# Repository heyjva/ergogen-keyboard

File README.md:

# ergogen-keyboard

Ergogen keyboard project, migrated to **KiCad 8** with a local preview/edit app.

This repo contains the full keyboard definition: a **split ergo board** with a
matrix, thumb cluster, rotary encoder and its own nice!nano controller **per
half**. It is a **wireless split** (independent MCU on each half, e.g. ZMK).
The numpad that used to live in the old `heyjva/ergogen` fork is **not** part of
this repo.

## Split layout: left + right

One `config.yaml` generates **both halves** as separate PCBs via ergogen's
`mirror`:

- The `points.zones.main` / `thumb` zones carry a `mirror:` block, so ergogen
  emits `mirror_*` points for the right half.
- `pcbs.main_left` selects source points (`where: -/mirror_/`); `pcbs.main_right`
  selects mirror points (`where: /mirror_/`) and anchors positioned footprints
  to `mirror_main_*` refs.
- The right half's **side-actuated power/reset switches** get `+180°` rotation
  so their actuators face the mirrored board edge.
- Both halves share the same net names (P11..P21, P2, etc.). That is safe
  because they are **separate PCBs / separate MCUs** — the nets never physically
  connect across boards.

Ergogen writes `output/pcbs/main_left.kicad_pcb` and
`output/pcbs/main_right.kicad_pcb`. The KiCad projects live in:

| Path | Description |
|------|-------------|
| `kicad/left/`  | Left half KiCad project. **Fully routed** + DRC-clean (JLCPCB rules). |
| `kicad/right/` | Right half KiCad project (mirror image). Generated, **not yet routed**. |
| `kicad/3d_models/` | Shared STEP/WRL 3D models (symlinked into each half). |

Build/regenerate a half's KiCad project from ergogen output:

```bash
node <ergogen> . -o output           # regenerate both PCBs
./kicad/build_kicad_project.sh right  # (re)build the right-half project
# ./kicad/build_kicad_project.sh left   # WARNING: wipes the routed left PCB
```

## Contents

| Path | Description |
|------|-------------|
| `config.yaml` | Ergogen definition (KiCad 8, Back-side hotswap, mirrored split). |
| `key.json` | Original KLE source, kept for reference. |
| `footprints/ceoloide/` | Vendored KiCad 8 footprints used by the board. |
| `output/` | Generated output (DXF outlines + `main_left`/`main_right` PCBs). |

## Footprints (KiCad 8)

The board uses these footprints from
[`ceoloide/ergogen-footprints`](https://github.com/ceoloide/ergogen-footprints),
vendored under `footprints/ceoloide/`:

- `switch_choc_v1_v2` — Kailh Choc hotswap switches
- `diode_tht_sod123` — per-key diodes
- `mcu_nice_nano` — nice!nano controller
- `encoder_evqwgd001` — Panasonic EVQWGD001 rotary encoder
- `battery_connector_jst_ph_2`, `power_switch_smd_side`,
  `reset_switch_smd_side`, `mounting_hole_plated`

Keys/diodes/MCU/encoder are on the **Back (`B`)** side; the side-actuated
power/reset switches are on the **Front (`F`)**. Each half is non-reversible on
its own; the *split* mirror is what produces the right half.

## Wiring notes (important for firmware)

The matrix uses 7 columns and 4 rows:

- Columns: `P21 P20 P19 P18 P17 P16 P15`
- Rows: `P14 P13 P12 P11`

The nice!nano does **not** break out physical pins named `P11`, `P12`, `P13`,
or `P17`. In `config.yaml` those logical nets are therefore routed onto spare
physical nice!nano pins, and the nice!view SPI signals are assigned as follows:

| Logical net | Physical nice!nano pin |
|-------------|------------------------|
| `P17` (index column) | `P4` |
| `P13` (home row) | `P5` |
| `P12` (top row) | `P6` |
| `P11` (num row) | `P7` |
| `MOSI` (display) | `P8` |
| `SCK` (display) | `P9` |
| `CS` (display) | `P3` |

The remaining matrix nets (`P21 P20 P19 P18 P16 P15 P14`) map 1:1 to the
same-named physical pins. **Update your firmware pin map to match the physical
pins above.** (In the original fork these four nets were never connected to the
MCU — this project fixes that.)

## 3D models

The footprints are wired to reference 3D models but the model asset files are
not included here. To see 3D renders in KiCad, drop the appropriate `.step` /
`.wrl` files into `models/` and point the footprints' `*_3dmodel_filename`
params at them. 3D models do **not** render in the browser preview — only in
KiCad.

## Previewing & editing locally

The preview/edit app is a patched fork of
[`ceoloide/ergogen-gui`](https://github.com/ceoloide/ergogen-gui) at
[`heyjva/ergogen-gui`](https://github.com/heyjva/ergogen-gui). It runs a local
web server and, unlike the stock GUI, includes a **"Save to File"** button that
writes changes straight back to this repo's `config.yaml` — and it works in
**Firefox / Zen**.

### One-time setup

```bash
# clone both repos as siblings
git clone https://github.com/heyjva/ergogen-keyboard.git
git clone https://github.com/heyjva/ergogen-gui.git

cd ergogen-gui
npm install -g pnpm   # if you don't have pnpm
PNPM_CONFIG_BLOCK_EXOTIC_SUBDEPS=false \
  ERGOGEN_VERSION=github:ceoloide/ergogen#v4.3.0 \
  pnpm install --no-frozen-lockfile
```

### Run it

```bash
cd ergogen-gui
./start.sh
```

This launches:

1. a tiny **save-helper** on `http://localhost:3001` (writes `config.yaml`), and
2. the **GUI** on `http://localhost:3000`.

Open <http://localhost:3000> in **Firefox / Zen**. The editor auto-loads this
repo's `config.yaml`. Edit it, then click **Save to File** (or press
**Ctrl/Cmd+S**) to write your changes back to `config.yaml` on disk. Commit with
git as usual.

> The save-helper is required because Firefox cannot write local files directly
> from a web page. It binds to `127.0.0.1` only and only ever writes this repo's
> `config.yaml`.

If you keep the repos somewhere other than as siblings, point the helper at the
file explicitly:

```bash
CONFIG_PATH=/absolute/path/to/ergogen-keyboard/config.yaml ./start.sh
```

## Regenerating outputs from the command line

The GUI is for previewing/editing. To regenerate the DXF/KiCad files on disk
from `config.yaml`, run Ergogen v4.3.0 against this folder:

```bash
# from a checkout of ceoloide/ergogen at branch v4.3.0
node /path/to/ergogen/src/cli.js . -o output
```

This reads `config.yaml` + `footprints/` and writes `output/`.

## Complete KiCad project (schematic + PCB)

Ergogen only produces a `.kicad_pcb` (footprints + net connectivity, no
schematic). The `kicad/` folder contains a **complete, openable KiCad project**
generated from that PCB:

| File | Description |
|------|-------------|
| `kicad/keyboard.kicad_pro` | KiCad project file (open this) |
| `kicad/keyboard.kicad_pcb` | The PCB (copy of `output/pcbs/main.kicad_pcb`) |
| `kicad/keyboard.kicad_sch` | Generated schematic |
| `kicad/keyboard-schematic.pdf` | Rendered schematic (preview) |
| `kicad/gen_schematic.py` | Schematic generator (uses KiCad's `pcbnew`) |
| `kicad/build_kicad_project.sh` | Regenerates the whole project |

Open **`kicad/keyboard.kicad_pro`** in KiCad.

### About the schematic

The schematic is generated from the PCB's netlist (KiCad has no built-in
PCB→schematic reverse). Each component is a real symbol laid out on a grid, and
connectivity is expressed with **global net labels** on each pin (the standard
approach for auto-generated keyboard schematics). It's electrically correct and
ERC-readable, but laid out on a grid rather than hand-drawn — useful for
verification, BOM, and reference, not a pretty hand-routed diagram.

### Regenerating the KiCad project

Requires KiCad installed (`pcbnew` python module + `kicad-cli`):

```bash
# after regenerating output/ with ergogen:
./kicad/build_kicad_project.sh
```

### Notes / expected DRC warnings

- **Unconnected items**: the PCB has nets but no routed traces (ergogen doesn't
  route) — route in KiCad. Not an error.
- **`invalid_outline` from ENC1**: the EVQWGD001 encoder footprint adds an
  Edge.Cuts roller cutout that reads as a secondary open contour. Harmless for
  the design; clean it up in KiCad's Edge.Cuts if desired.
- **lib_footprint / lib_symbol warnings**: footprints are embedded in the PCB
  and standard KiCad symbol libs are used; these "library not in config"
  warnings are cosmetic.

### JLCPCB design rules

The project is pre-configured for JLCPCB's standard **2-layer, 1oz FR-4**
process (their cheapest tier), so DRC catches anything they can't make:

- Numeric constraints live in `kicad/keyboard.kicad_pro`
  (`board.design_settings.rules`): min track/clearance 0.1 mm, min via
  0.45 mm / 0.3 mm drill, min PTH drill 0.3 mm, min hole-to-hole 0.5 mm,
  min copper-to-edge 0.2 mm, min silk text 1.0 mm. These are JLCPCB's true
  standard-process minimums for 1oz 2-layer.
- The auto-router routes down to these limits (0.1 mm track/space, 0.1 mm
  hole-to-copper). That is manufacturable at JLCPCB but leaves little margin;
  the default net class uses a more comfortable 0.25 mm track / 0.1 mm space.
- JLC-specific checks (annular ring, edge clearance, hole-to-hole, silk
  width/height, silk-to-pad, SMD pad clearance) are in
  `kicad/keyboard.kicad_dru`. Note the via annular-ring rule is 0.05 mm:
  0.45 mm-via/0.3 mm-hole is a standard no-extra-cost JLC via; the 0.13 mm
  annular guideline applies to component PTH pads, not tented vias.
- These files are **not** overwritten by `build_kicad_project.sh` (which only
  regenerates the `.kicad_pcb`/`.kicad_sch`), so the rules persist across
  rebuilds. The router's "Fix DRC settings after routing" option WILL rewrite
  the `.kicad_pro` constraints, so re-check them after routing.
- Source: <https://jlcpcb.com/capabilities/pcb-capabilities>

Run a rules check any time with:

```bash
kicad-cli pcb drc kicad/keyboard.kicad_pcb --severity-error
```

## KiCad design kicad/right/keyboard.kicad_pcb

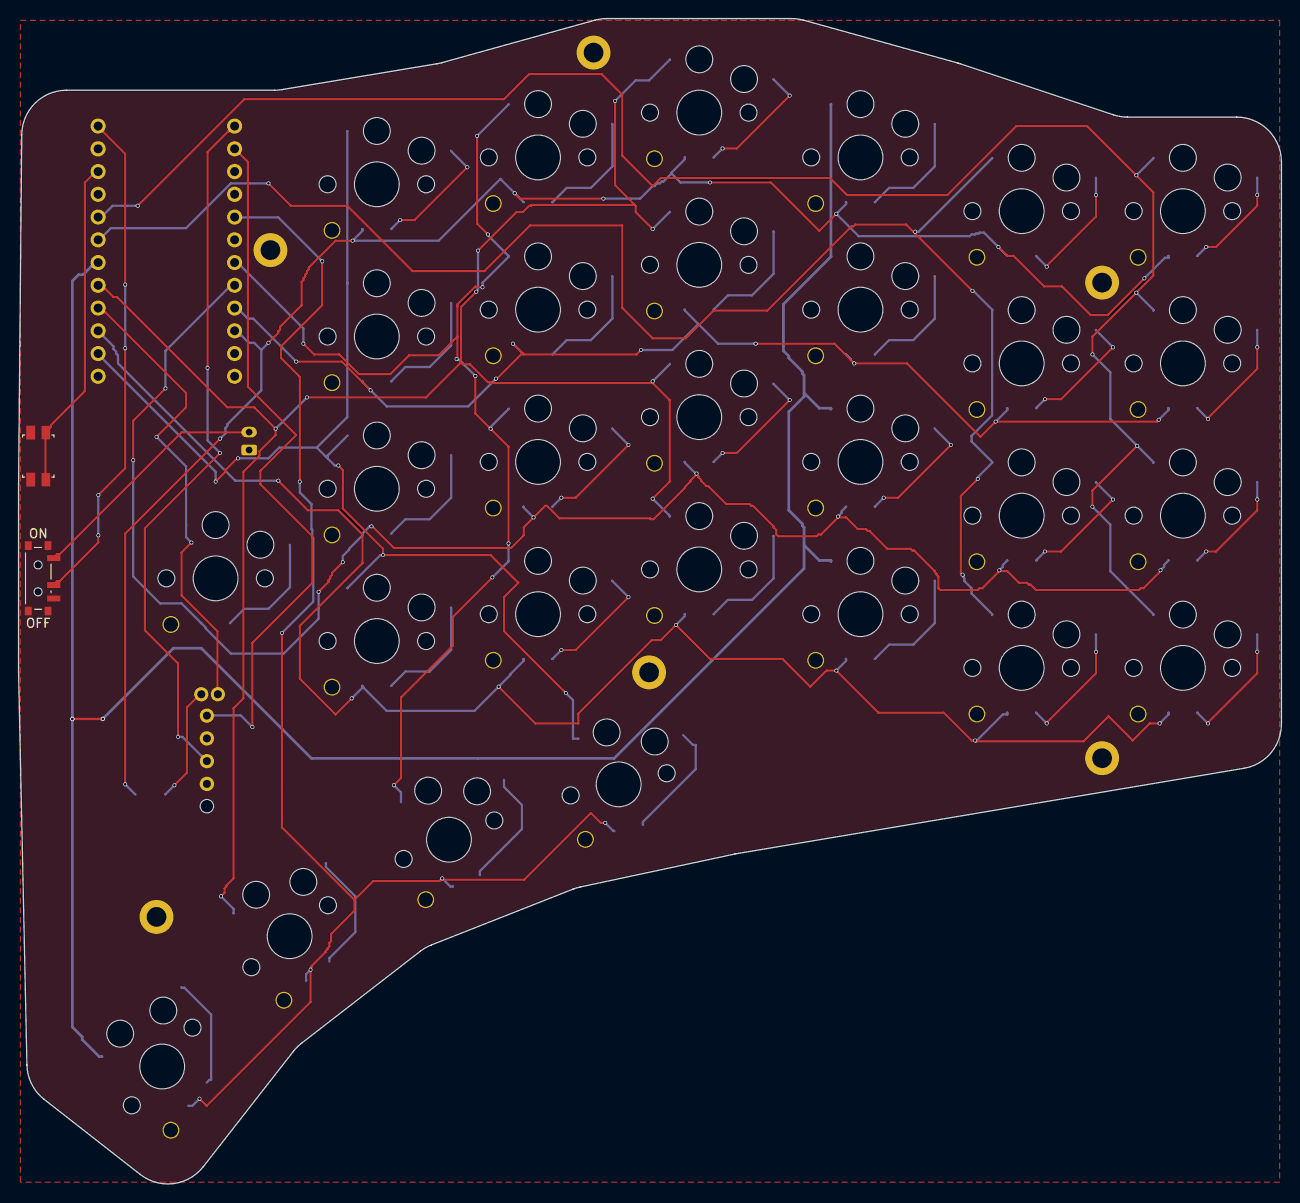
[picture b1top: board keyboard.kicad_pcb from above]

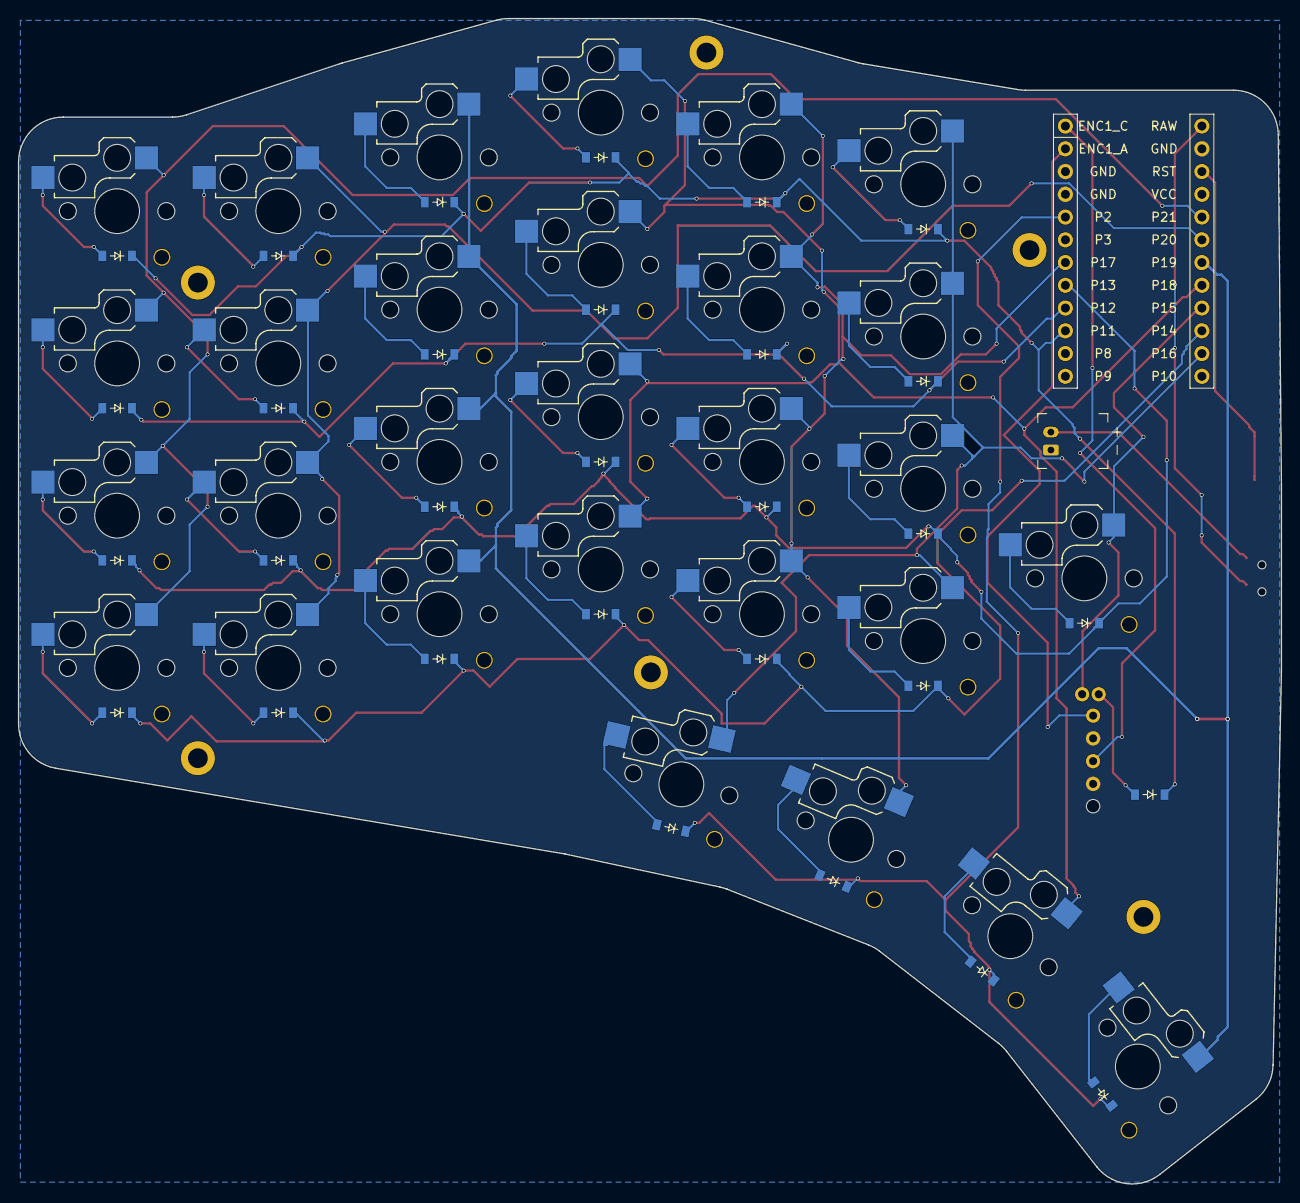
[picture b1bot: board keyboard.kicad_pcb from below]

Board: 2 copper layers, 141.0 x 130.1 mm, 70 parts (68 on the bottom side), 48 nets.

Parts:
D1, D2, D3, D4, D5, D6, D7, D8, D9, D10, D11, D12, D13, D14, D15, D16, D17, D18, D19, D20, D21, D22, D23, D24, D25, D26, D27, D28, D29, D30: diode_tht_sod123
ENC1: encoder_evqwgd001
H1, H2, H3, H4, H5, H6: mounting_hole_plated
JST1: battery_connector_jst_ph_2
MCU1: mcu_nice_nano
PWR1: power_switch_smd_side
RST1: reset_switch_smd_side
S1, S2, S3, S4, S5, S6, S7, S8, S9, S10, S11, S12, S13, S14, S15, S16, S17, S18, S19, S20, S21, S22, S23, S24, S25, S26, S27, S28, S29: switch_choc_v1_v2

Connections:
BAT_P: JST1.2, PWR1.1
ENC1_A: ENC1.A, MCU1.2
ENC1_C: ENC1.C, MCU1.1
ENC1_SW: D30.2, ENC1.2
GND: ENC1.B, ENC1.D, JST1.1, MCU1.3, MCU1.4, MCU1.23, RST1.1, RST1.3
P2: D26.1, D27.1, D28.1, D29.1, MCU1.5
P11: D4.1, D8.1, D12.1, D16.1, D20.1, D24.1, D30.1, MCU1.10
P12: D3.1, D7.1, D11.1, D15.1, D19.1, D23.1, MCU1.9
P13: D2.1, D6.1, D10.1, D14.1, D18.1, D22.1, D25.1, MCU1.8
P14: D1.1, D5.1, D9.1, D13.1, D17.1, D21.1, MCU1.15
P15: ENC1.1, MCU1.16, S25.1
P16: MCU1.14, S21.1, S22.1, S23.1, S24.1, S26.1
P17: MCU1.7, S17.1, S18.1, S19.1, S20.1, S27.1
P18: MCU1.17, S13.1, S14.1, S15.1, S16.1, S28.1
P19: MCU1.18, S9.1, S10.1, S11.1, S12.1, S29.1
P20: MCU1.19, S5.1, S6.1, S7.1, S8.1
P21: MCU1.20, S1.1, S2.1, S3.1, S4.1
RAW: MCU1.24, PWR1.2
RST: MCU1.22, RST1.2, RST1.4
mirror_home_cluster: D27.2, S27.2
mirror_index_bottom: D17.2, S17.2
mirror_index_home: D18.2, S18.2
mirror_index_num: D20.2, S20.2
mirror_index_top: D19.2, S19.2
mirror_inner_bottom: D21.2, S21.2
mirror_inner_cluster: D26.2, S26.2
mirror_inner_home: D22.2, S22.2
mirror_inner_num: D24.2, S24.2
mirror_inner_top: D23.2, S23.2
mirror_middle_bottom: D13.2, S13.2
mirror_middle_home: D14.2, S14.2
mirror_middle_num: D16.2, S16.2
mirror_middle_top: D15.2, S15.2
mirror_oouter_cluster: D29.2, S29.2
mirror_outer_bottom: D1.2, S1.2
mirror_outer_cluster: D28.2, S28.2
mirror_outer_home: D2.2, S2.2
mirror_outer_num: D4.2, S4.2
mirror_outer_top: D3.2, S3.2
mirror_pinky_bottom: D5.2, S5.2
mirror_pinky_home: D6.2, S6.2
mirror_pinky_num: D8.2, S8.2
mirror_pinky_top: D7.2, S7.2
mirror_ring_bottom: D9.2, S9.2
mirror_ring_home: D10.2, S10.2
mirror_ring_num: D12.2, S12.2
mirror_ring_top: D11.2, S11.2
mirror_single_home: D25.2, S25.2

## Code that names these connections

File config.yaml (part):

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          C: ENC1_C
          D: GND
          from: P15       # column net (switch pin 1)
          to: ENC1_SW     # unique matrix node (switch pin 2)
          encoder_3dmodel_filename: "${KIPRJMOD}/3d_models/EVQWGD001_Encoder.wrl"
          encoder_3dmodel_xyz_scale: [1, 1, 1]
          encoder_3dmodel_xyz_rotation: [0, 180, 0]
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          battery_connector_3dmodel_xyz_rotation: [0, 0, 0]
          battery_connector_3dmodel_xyz_offset: [0, 0, 0]
      # ---- Power switch (SMD side-actuated), Back side ----
      # Switches battery positive (BAT_P) to the nice!nano RAW pin.
      power_switch:
        what: ceoloide/power_switch_smd_side
        where:
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          C: ENC1_C
          D: GND
          from: P15       # column net (switch pin 1)
          to: ENC1_SW     # unique matrix node (switch pin 2)
          encoder_3dmodel_filename: "${KIPRJMOD}/3d_models/EVQWGD001_Encoder.wrl"
          encoder_3dmodel_xyz_scale: [1, 1, 1]
          encoder_3dmodel_xyz_rotation: [0, 180, 0]
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          battery_connector_3dmodel_xyz_rotation: [0, 0, 0]
          battery_connector_3dmodel_xyz_offset: [0, 0, 0]
      # ---- Power switch (SMD side-actuated), Back side ----
      # Switches battery positive (BAT_P) to the nice!nano RAW pin.
      power_switch:
        what: ceoloide/power_switch_smd_side
        where:
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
